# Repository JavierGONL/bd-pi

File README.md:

# BD-π

------------
## integrantes: 
* Kevin Javier Gonzalez Luna
* David Alejandro Montes Rodrigrez
* Rafael David Martinez Ovallos
------------

<div align='center'>
<figure> </br>
<figcaption><b></b></figcaption></figure>
</div>

#### 🤖[wiki del proyecto](https://github.com/JavierGONL/bd-pi/wiki)🤖

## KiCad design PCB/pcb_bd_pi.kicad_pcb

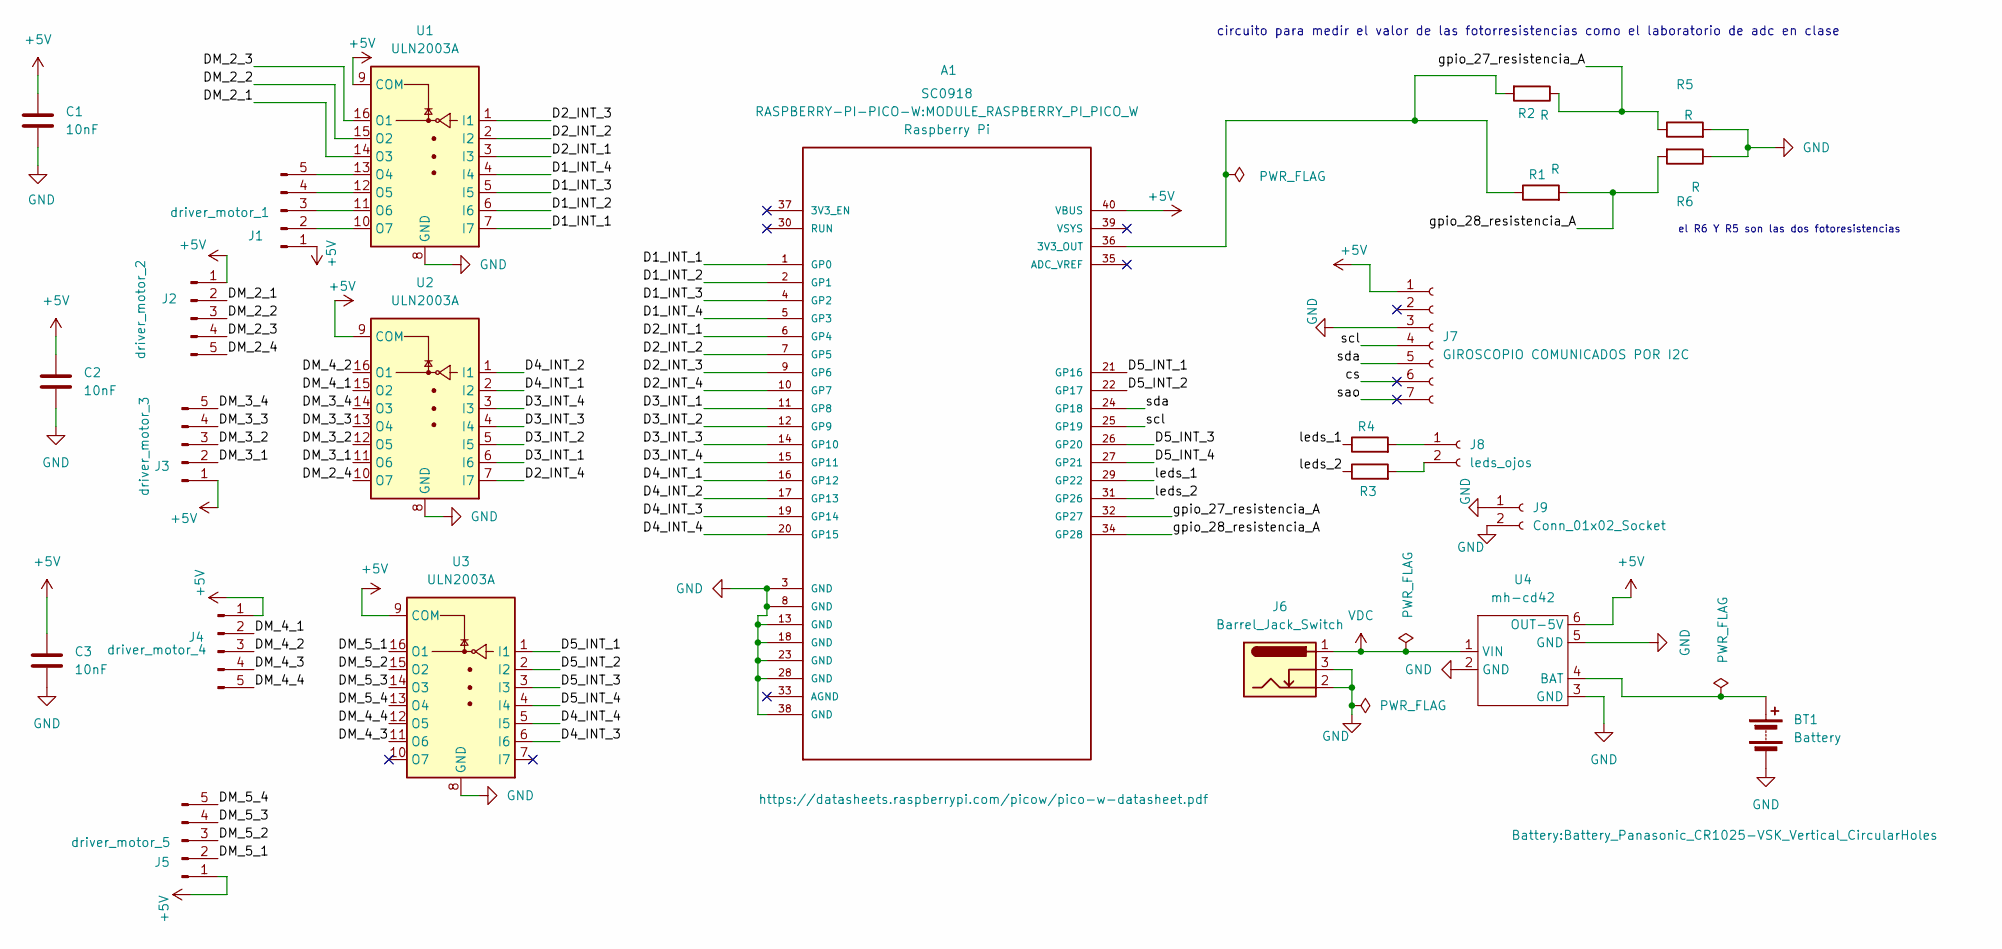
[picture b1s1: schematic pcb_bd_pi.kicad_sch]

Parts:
A1: SC0918; MODULE_RASPBERRY_PI_PICO_W; PARTREV 1.6
BT1: Battery; Battery_Panasonic_CR1025-VSK_Vertical_CircularHoles
C1, C2, C3: 10nF; C_Disc_D7.5mm_W5.0mm_P5.00mm
J1: driver_motor_1; PinHeader_1x05_P2.54mm_Vertical
J2: driver_motor_2; PinHeader_1x05_P2.54mm_Vertical
J3: driver_motor_3; PinHeader_1x05_P2.54mm_Vertical
J4: driver_motor_4; PinHeader_1x05_P2.54mm_Vertical
J5: driver_motor_5; PinHeader_1x05_P2.54mm_Vertical
J6: Barrel_Jack_Switch; BarrelJack_Horizontal
J7: GIROSCOPIO COMUNICADOS POR I2C; PinSocket_1x07_P2.54mm_Vertical
J8: leds_ojos; PinHeader_1x02_P2.54mm_Vertical
J9: Conn_01x02_Socket; PinHeader_1x02_P2.54mm_Vertical
R1, R2, R3, R4, R5, R6: R; R_Axial_DIN0204_L3.6mm_D1.6mm_P2.54mm_Vertical
U1, U2, U3: ULN2003A; DIP-16_W7.62mm_Socket
U4: mh-cd42

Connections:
+5V: A1.40 (VBUS), C1.1, C2.1, C3.1, J1.1, J2.1, J3.1, J4.1, J5.1, J7.1, U1.9 (COM), U2.9 (COM), U3.9 (COM), U4.6 (OUT-5V)
/D1_INT_1: A1.1 (GP0), U1.7 (I7)
/D1_INT_2: A1.2 (GP1), U1.6 (I6)
/D1_INT_3: A1.4 (GP2), U1.5 (I5)
/D1_INT_4: A1.5 (GP3), U1.4 (I4)
/D2_INT_1: A1.6 (GP4), U1.3 (I3)
/D2_INT_2: A1.7 (GP5), U1.2 (I2)
/D2_INT_3: A1.9 (GP6), U1.1 (I1)
/D2_INT_4: A1.10 (GP7), U2.7 (I7)
/D3_INT_1: A1.11 (GP8), U2.6 (I6)
/D3_INT_2: A1.12 (GP9), U2.5 (I5)
/D3_INT_3: A1.14 (GP10), U2.4 (I4)
/D3_INT_4: A1.15 (GP11), U2.3 (I3)
/D4_INT_1: A1.16 (GP12), U2.2 (I2)
/D4_INT_2: A1.17 (GP13), U2.1 (I1)
/D4_INT_3: A1.19 (GP14), U3.6 (I6)
/D4_INT_4: A1.20 (GP15), U3.5 (I5)
/D5_INT_1: A1.21 (GP16), U3.1 (I1)
/D5_INT_2: A1.22 (GP17), U3.2 (I2)
/D5_INT_3: A1.26 (GP20), U3.3 (I3)
/D5_INT_4: A1.27 (GP21), U3.4 (I4)
/DM_2_1: J2.2, U1.14 (O3)
/DM_2_2: J2.3, U1.15 (O2)
/DM_2_3: J2.4, U1.16 (O1)
/DM_2_4: J2.5, U2.10 (O7)
/DM_3_1: J3.2, U2.11 (O6)
/DM_3_2: J3.3, U2.12 (O5)
/DM_3_3: J3.4, U2.13 (O4)
/DM_3_4: J3.5, U2.14 (O3)
/DM_4_1: J4.2, U2.15 (O2)
/DM_4_2: J4.3, U2.16 (O1)
/DM_4_3: J4.4, U3.11 (O6)
/DM_4_4: J4.5, U3.12 (O5)
/DM_5_1: J5.2, U3.16 (O1)
/DM_5_2: J5.3, U3.15 (O2)
/DM_5_3: J5.4, U3.14 (O3)
/DM_5_4: J5.5, U3.13 (O4)
/cs: J7.6
/gpio_27_resistencia_A: A1.32 (GP27), R2.1, R5.1
/gpio_28_resistencia_A: A1.34 (GP28), R1.2, R6.2
/leds_1: A1.29 (GP22), R4.1
/leds_2: A1.31 (GP26), R3.1
/sao: J7.7
/scl: A1.25 (GP19), J7.4
/sda: A1.24 (GP18), J7.5
GND: A1.3 (GND), A1.8 (GND), A1.13 (GND), A1.18 (GND), A1.23 (GND), A1.28 (GND), A1.38 (GND), BT1.2 (-), C1.2, C2.2, C3.2, J6.2, J6.3, J7.3, J9.1, J9.2, R5.2, R6.1, U1.8 (GND), U2.8 (GND), U3.8 (GND), U4.2 (GND), U4.3 (GND), U4.5 (GND)
unnamed: A1.36 (3V3_OUT), R1.1, R2.2
unnamed: BT1.1 (+), U4.4 (BAT)
unnamed: J1.2, U1.10 (O7)
unnamed: J1.3, U1.11 (O6)
unnamed: J1.4, U1.12 (O5)
unnamed: J1.5, U1.13 (O4)
unnamed: J8.1, R4.2
unnamed: J8.2, R3.2
VDC: J6.1, U4.1 (VIN)

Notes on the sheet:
circuito para medir el valor de las fotorresistencias como el laboratorio de adc en clase
el R6 Y R5 son las dos fotoresistencias

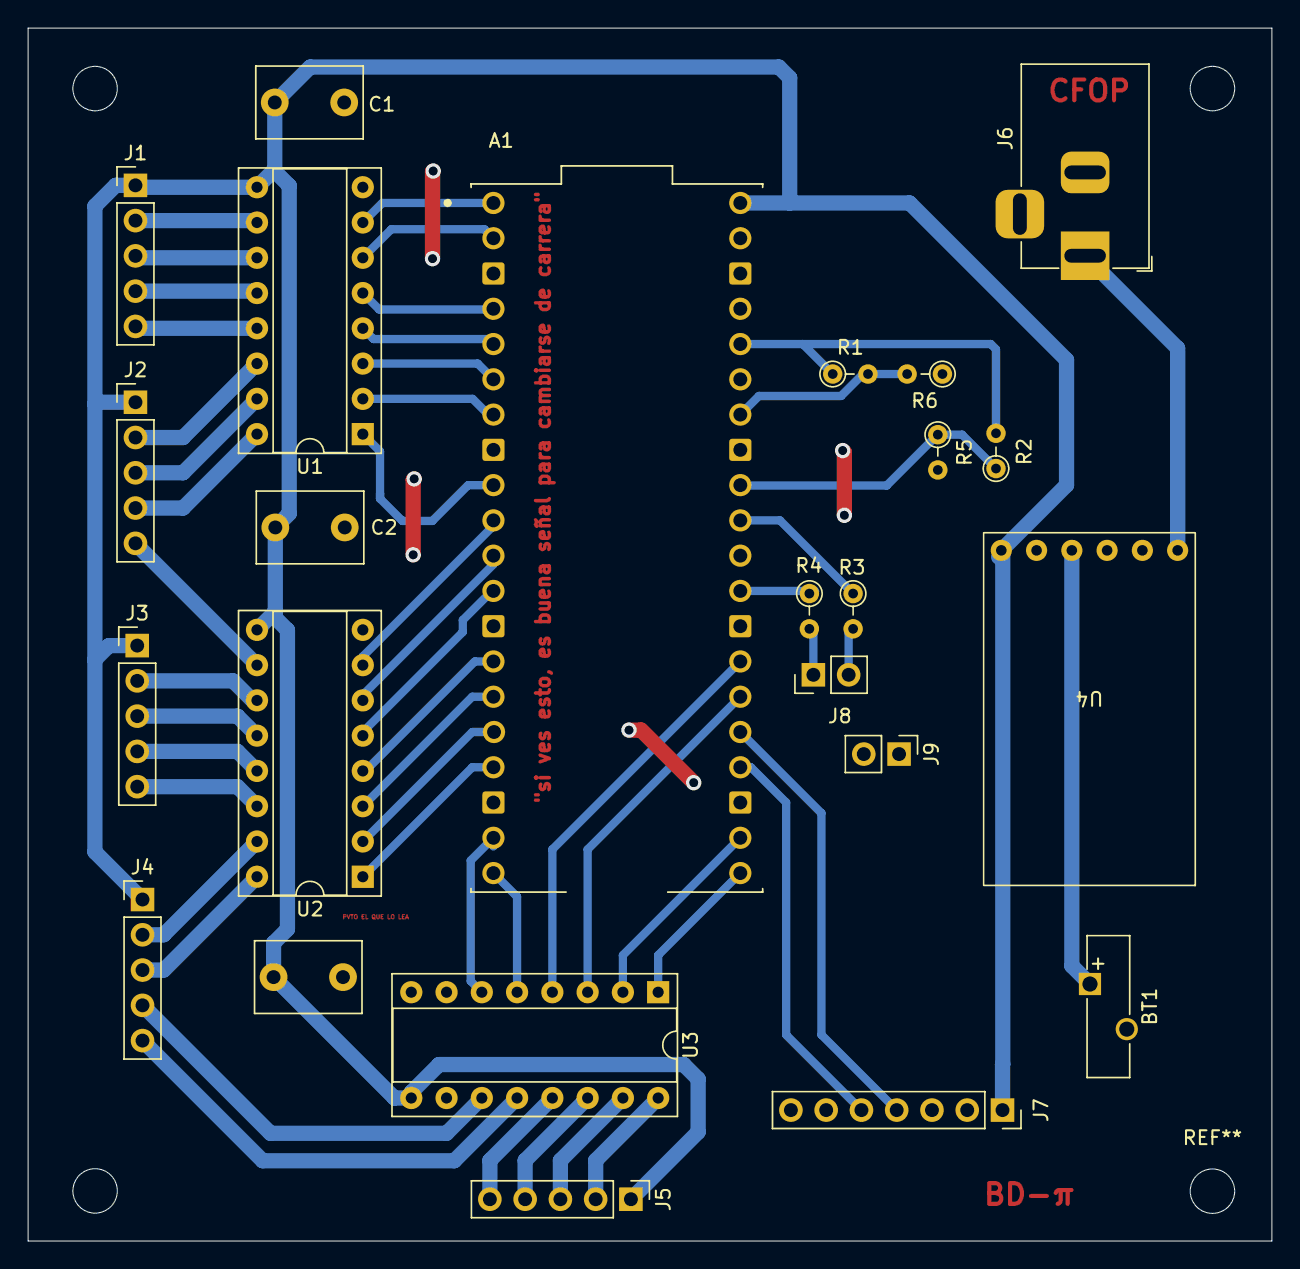
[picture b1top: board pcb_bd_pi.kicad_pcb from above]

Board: 2 copper layers, 89.6 x 87.4 mm, 24 parts (0 on the bottom side), 53 nets.

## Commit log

2024-09-11 Implementar Imagenes
2024-09-17 Create bd-pi.code-workspace
2024-09-25 Create prueba_conectividad
2024-09-25 App BDpi
2024-09-25 Agregar Imagenes
2024-09-25 Imagenes Modelados
